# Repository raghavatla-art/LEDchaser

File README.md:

# LEDchaser
This is my first PCB design and it is a ring oscillator LED chaser that uses THT transistors. This is also my first project for Hack Club after hearing about it from my friends. I had to learn basic electronic components and it was quite fun.
## Visuals
3D Render

PCB Layout

My Schematics

# BOM

- 4 10uF capacitors
- 4 470ohm resistors
- 4 47kohm resistors
- 3 LEDs
- 4 2N3904 transistors
- 2 battery cells
- 1 push button switch

Falstad link:https://www.falstad.com/s.php?s=uAG2Ck \
Made by [@Raghav.atla](https://slack.com) on slack!

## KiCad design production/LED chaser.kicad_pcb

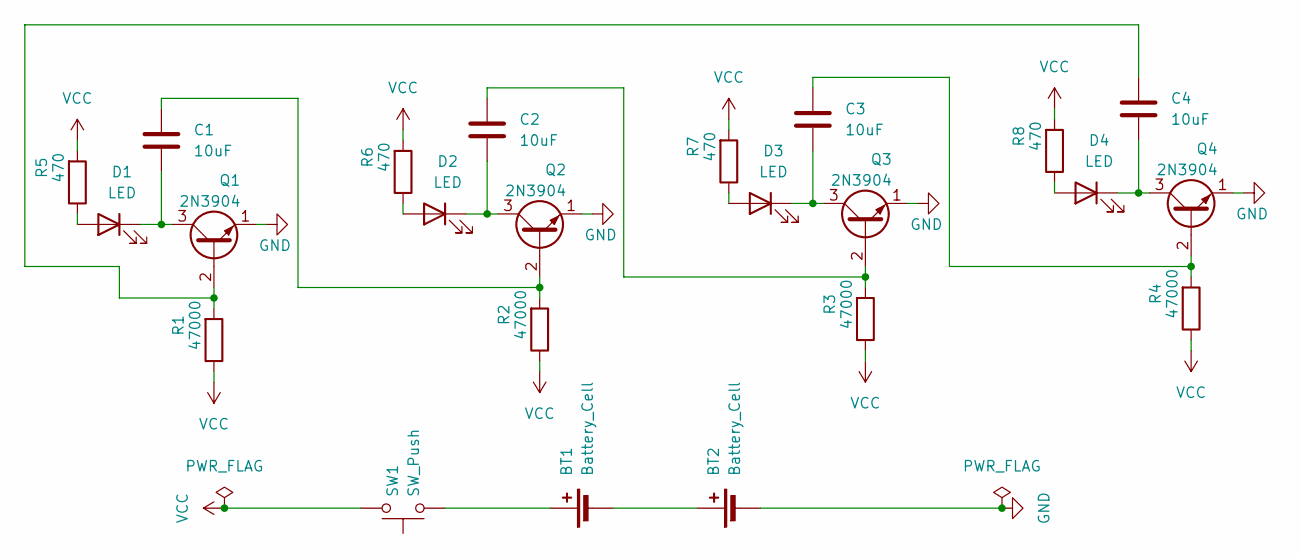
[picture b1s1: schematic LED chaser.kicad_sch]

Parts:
BT1, BT2: Battery_Cell; BatteryHolder_Keystone_3034_1x20mm
C1, C2, C3, C4: 10uF; C_Disc_D5.0mm_W2.5mm_P2.50mm
D1, D2, D3, D4: LED; LED_D3.0mm
Q1, Q2, Q3, Q4: 2N3904; TO-92_Inline
R1, R2, R3, R4: 47000; R_Axial_DIN0204_L3.6mm_D1.6mm_P5.08mm_Vertical
R5, R6, R7, R8: 470; R_Axial_DIN0204_L3.6mm_D1.6mm_P5.08mm_Vertical
SW1: SW_Push; SW_PUSH_6mm

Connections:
GND: BT2.2 (-), Q1.1 (E), Q2.1 (E), Q3.1 (E), Q4.1 (E)
unnamed: BT1.1 (+), SW1.1
unnamed: BT1.2 (-), BT2.1 (+)
unnamed: D1.2 (A), R5.1
unnamed: C1.2, D1.1 (K), Q1.3 (C)
unnamed: D2.2 (A), R6.1
unnamed: C2.2, D2.1 (K), Q2.3 (C)
unnamed: D3.2 (A), R7.1
unnamed: C3.2, D3.1 (K), Q3.3 (C)
unnamed: D4.2 (A), R8.1
unnamed: C4.2, D4.1 (K), Q4.3 (C)
unnamed: C4.1, Q1.2 (B), R1.2
unnamed: C1.1, Q2.2 (B), R2.2
unnamed: C2.1, Q3.2 (B), R3.2
unnamed: C3.1, Q4.2 (B), R4.2
VCC: R1.1, R2.1, R3.1, R4.1, R5.2, R6.2, R7.2, R8.2, SW1.2

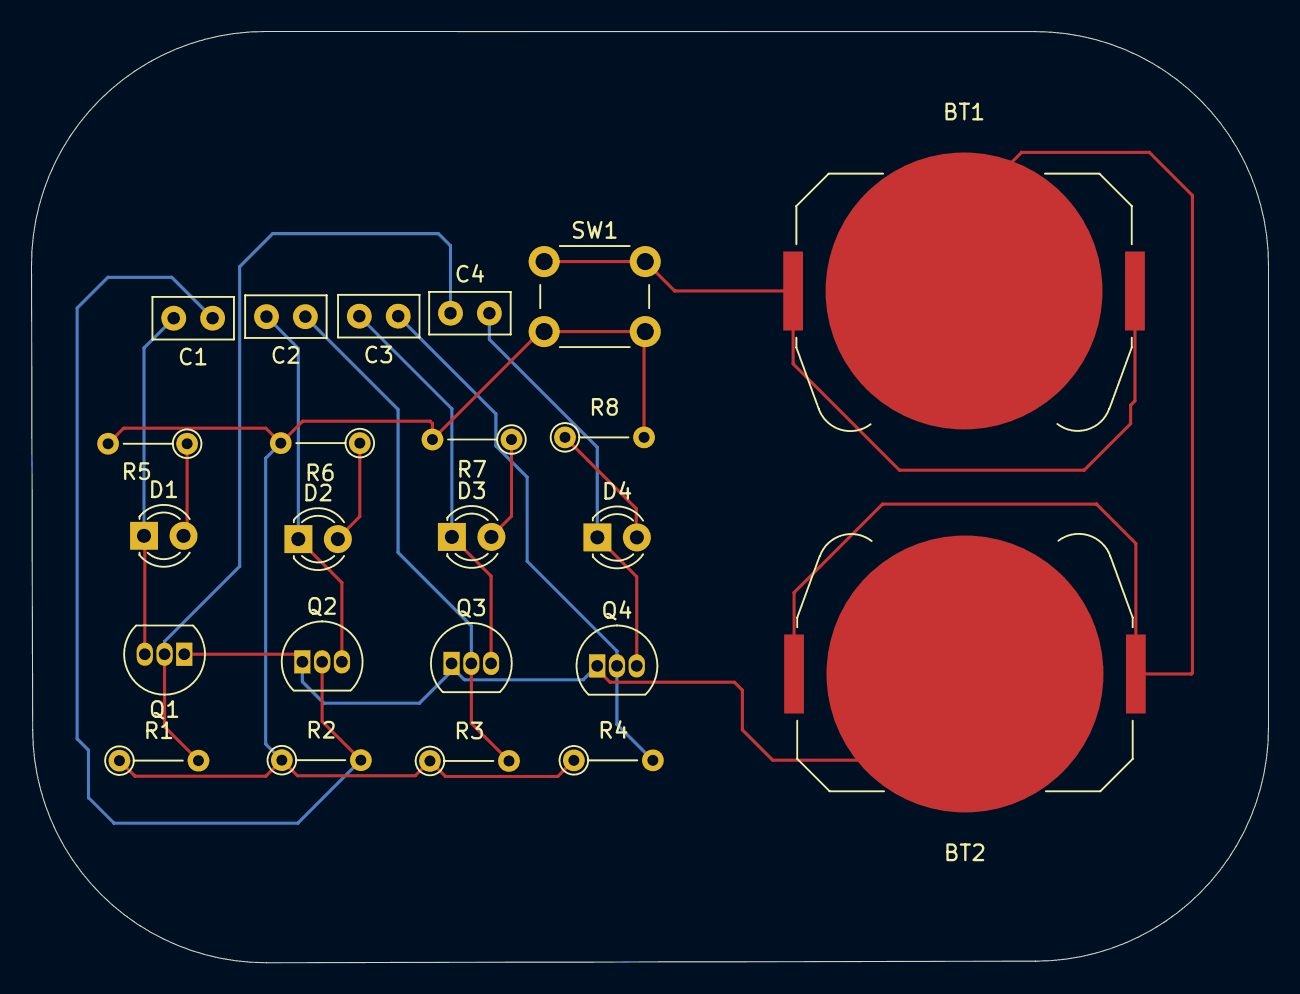
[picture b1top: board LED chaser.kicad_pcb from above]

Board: 2 copper layers, 79.5 x 59.9 mm, 23 parts (0 on the bottom side), 16 nets.
